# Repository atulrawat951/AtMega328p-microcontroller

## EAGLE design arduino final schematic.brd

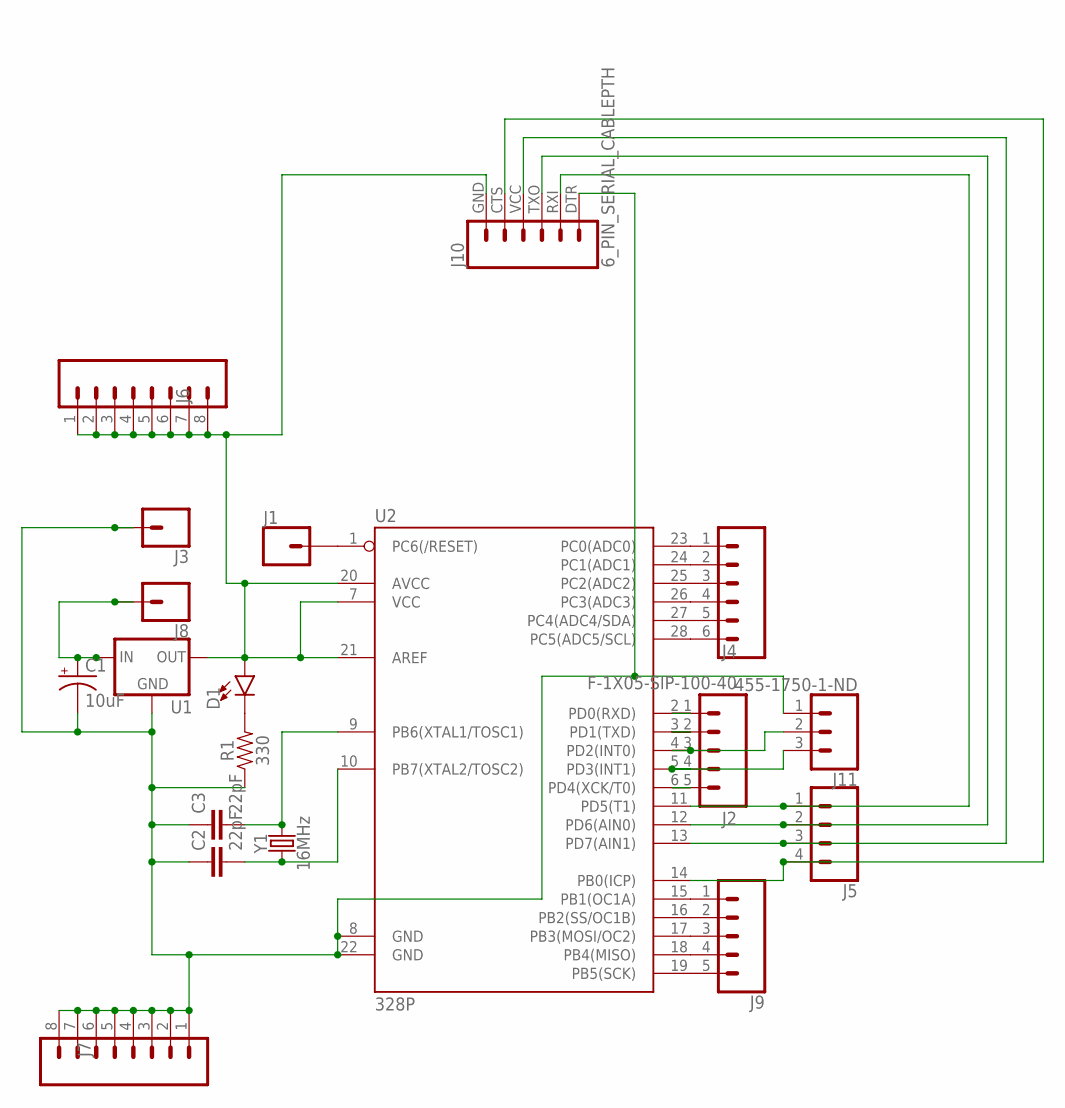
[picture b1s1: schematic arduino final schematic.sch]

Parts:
C1: 10uF; CPOL-RADIAL-2.5MM-5MM
C2, C3: 22pF; CAP-PTH-2.54
D1: LED3MM; LED_3MM
J1, J3, J8: CONN_01; 1X01
J2: F-1X05-SIP-100-40; 1X05
J4: CONN_06NO_SILK_FEMALE_PTH; 1X06_NO_SILK
J5: CONN_04PTH; 1X04
J6, J7: CONN_08"; 1X08
J9: CONN_05; 1X05
J10: 6_PIN_SERIAL_CABLEPTH; FTDI_BASIC
J11: 455-1750-1-ND; 1X03
R1: 330; AXIAL-0.3
U1: V_REG_78XX-TO-220; TO-220-ALT
U2: 328P; DIP28
Y1: 16MHz; HC49US

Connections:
unnamed: C1.1 (+), J8.1, U1.IN
unnamed: D1.A, J6.1, J6.2, J6.3, J6.4, J6.5, J6.6, J6.7, J6.8, J10.GND (6), U1.OUT, U2.7 (VCC), U2.20 (AVCC), U2.21 (AREF)
unnamed: C1.2 (-), C2.1, C3.1, J3.1, J7.1, J7.2, J7.3, J7.4, J7.5, J7.6, J7.7, J7.8, J10.DTR (1), J11.1, R1.P$1 (1), U1.GND, U2.8 (GND), U2.22 (GND)
unnamed: D1.K (C), R1.P$2 (2)
unnamed: C3.2, U2.9 (PB6(XTAL1/TOSC1)), Y1.2
unnamed: C2.2, U2.10 (PB7(XTAL2/TOSC2)), Y1.1
unnamed: J9.1, U2.15 (PB1(OC1A))
unnamed: J4.1, U2.23 (PC0(ADC0))
unnamed: J4.2, U2.24 (PC1(ADC1))
unnamed: J4.3, U2.25 (PC2(ADC2))
unnamed: J4.4, U2.26 (PC3(ADC3))
unnamed: J4.5, U2.27 (PC4(ADC4/SDA))
unnamed: J4.6, U2.28 (PC5(ADC5/SCL))
unnamed: J2.1, U2.2 (PD0(RXD))
unnamed: J2.2, U2.3 (PD1(TXD))
unnamed: J2.3, J11.2, U2.4 (PD2(INT0))
unnamed: J2.4, J11.3, U2.5 (PD3(INT1))
unnamed: J2.5, U2.6 (PD4(XCK/T0))
unnamed: J9.2, U2.16 (PB2(SS/OC1B))
unnamed: J9.3, U2.17 (PB3(MOSI/OC2))
unnamed: J9.4, U2.18 (PB4(MISO))
unnamed: J9.5, U2.19 (PB5(SCK))
unnamed: J1.1, U2.1 (PC6(/RESET))
unnamed: J5.1, J10.RXI (2), U2.11 (PD5(T1))
unnamed: J5.2, J10.TXO (3), U2.12 (PD6(AIN0))
unnamed: J5.3, J10.VCC (4), U2.13 (PD7(AIN1))
unnamed: J5.4, J10.CTS (5), U2.14 (PB0(ICP))

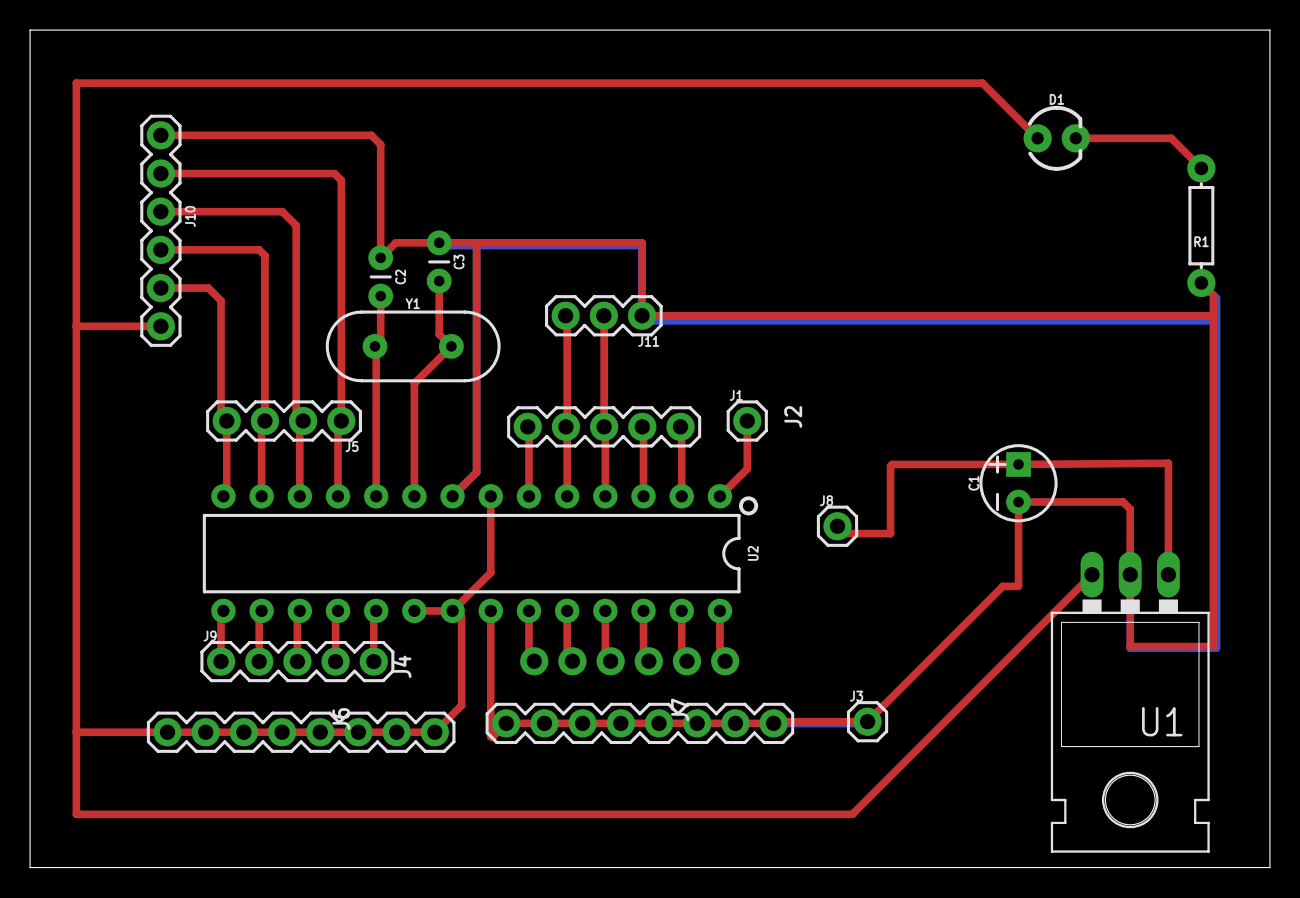
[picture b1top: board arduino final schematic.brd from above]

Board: 2 copper layers, 82.5 x 55.7 mm, 19 parts (0 on the bottom side), 27 nets.

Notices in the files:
parts and their libraries:
SparkFun-Capacitors: Licensing: Creative Commons ShareAlike 4.0 International - https://creativecommons.org/licenses/by-sa/4.0
